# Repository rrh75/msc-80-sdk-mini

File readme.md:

# MSC-80 mini 8080A single board computer
This is a modified version of old Intel MSC-80 SDK, which utilize the Intel 8080A 8-bit processor. In this modification I tried to reduce size of pcb and number of ICs to minimum.

I have a bunch of old soviet era 8080 CPU clones, which are relatively chip now.
In current revision 74LS93 divider was replaces by 74LS92 divider, with is naturally /12, /6 or /3 divider. The board on picture below shows previous version with /16 divider (КР1553ИЕ5), configurated as /6.

The board has 2KB of UV EEPROM, 2KB of SRAM and 8251 UART controller for communication with console. In this version I used a 16,588MHz crystal to get the 1,8432MHz clock output, which could be divided by 6 or by 12 ro get correct baudrates.
Adress decoding also simplified comparing to original design and done by 3NAND gates. The address map are follow:
* ROM: 0000H-07FFH
* RAM: 1000H-17FFH
* UART: 0FAH
  
This version of board does not provide address buffering, but it is enough to work with onboard chips.
Communication with terminal program on the host computer is done via com port. Depending of the software and divide ratio it could be up to 19200 kb/s, RTS/CTS handshake, 8n1.

Since the processor use three voltages to operate, the board has build-in -5V charge pump circuit, but still required +5V and +12V. I used simple step-up converter to get +12V from +5V, but it was mounted outside the board. Power consumption from +5V is about 600 mA.
# Software
I've tried this board with original firmware, but since it was very old and intended to work with teletype, original monitor have very limited set of commands.

I found nice solution with GW monitor, with small modifications of addresses in source code it is also work and feet in existing ROM.

There also simple test program to test the 8251 communication functions.
Also I want to try 1K BASIC on this board.

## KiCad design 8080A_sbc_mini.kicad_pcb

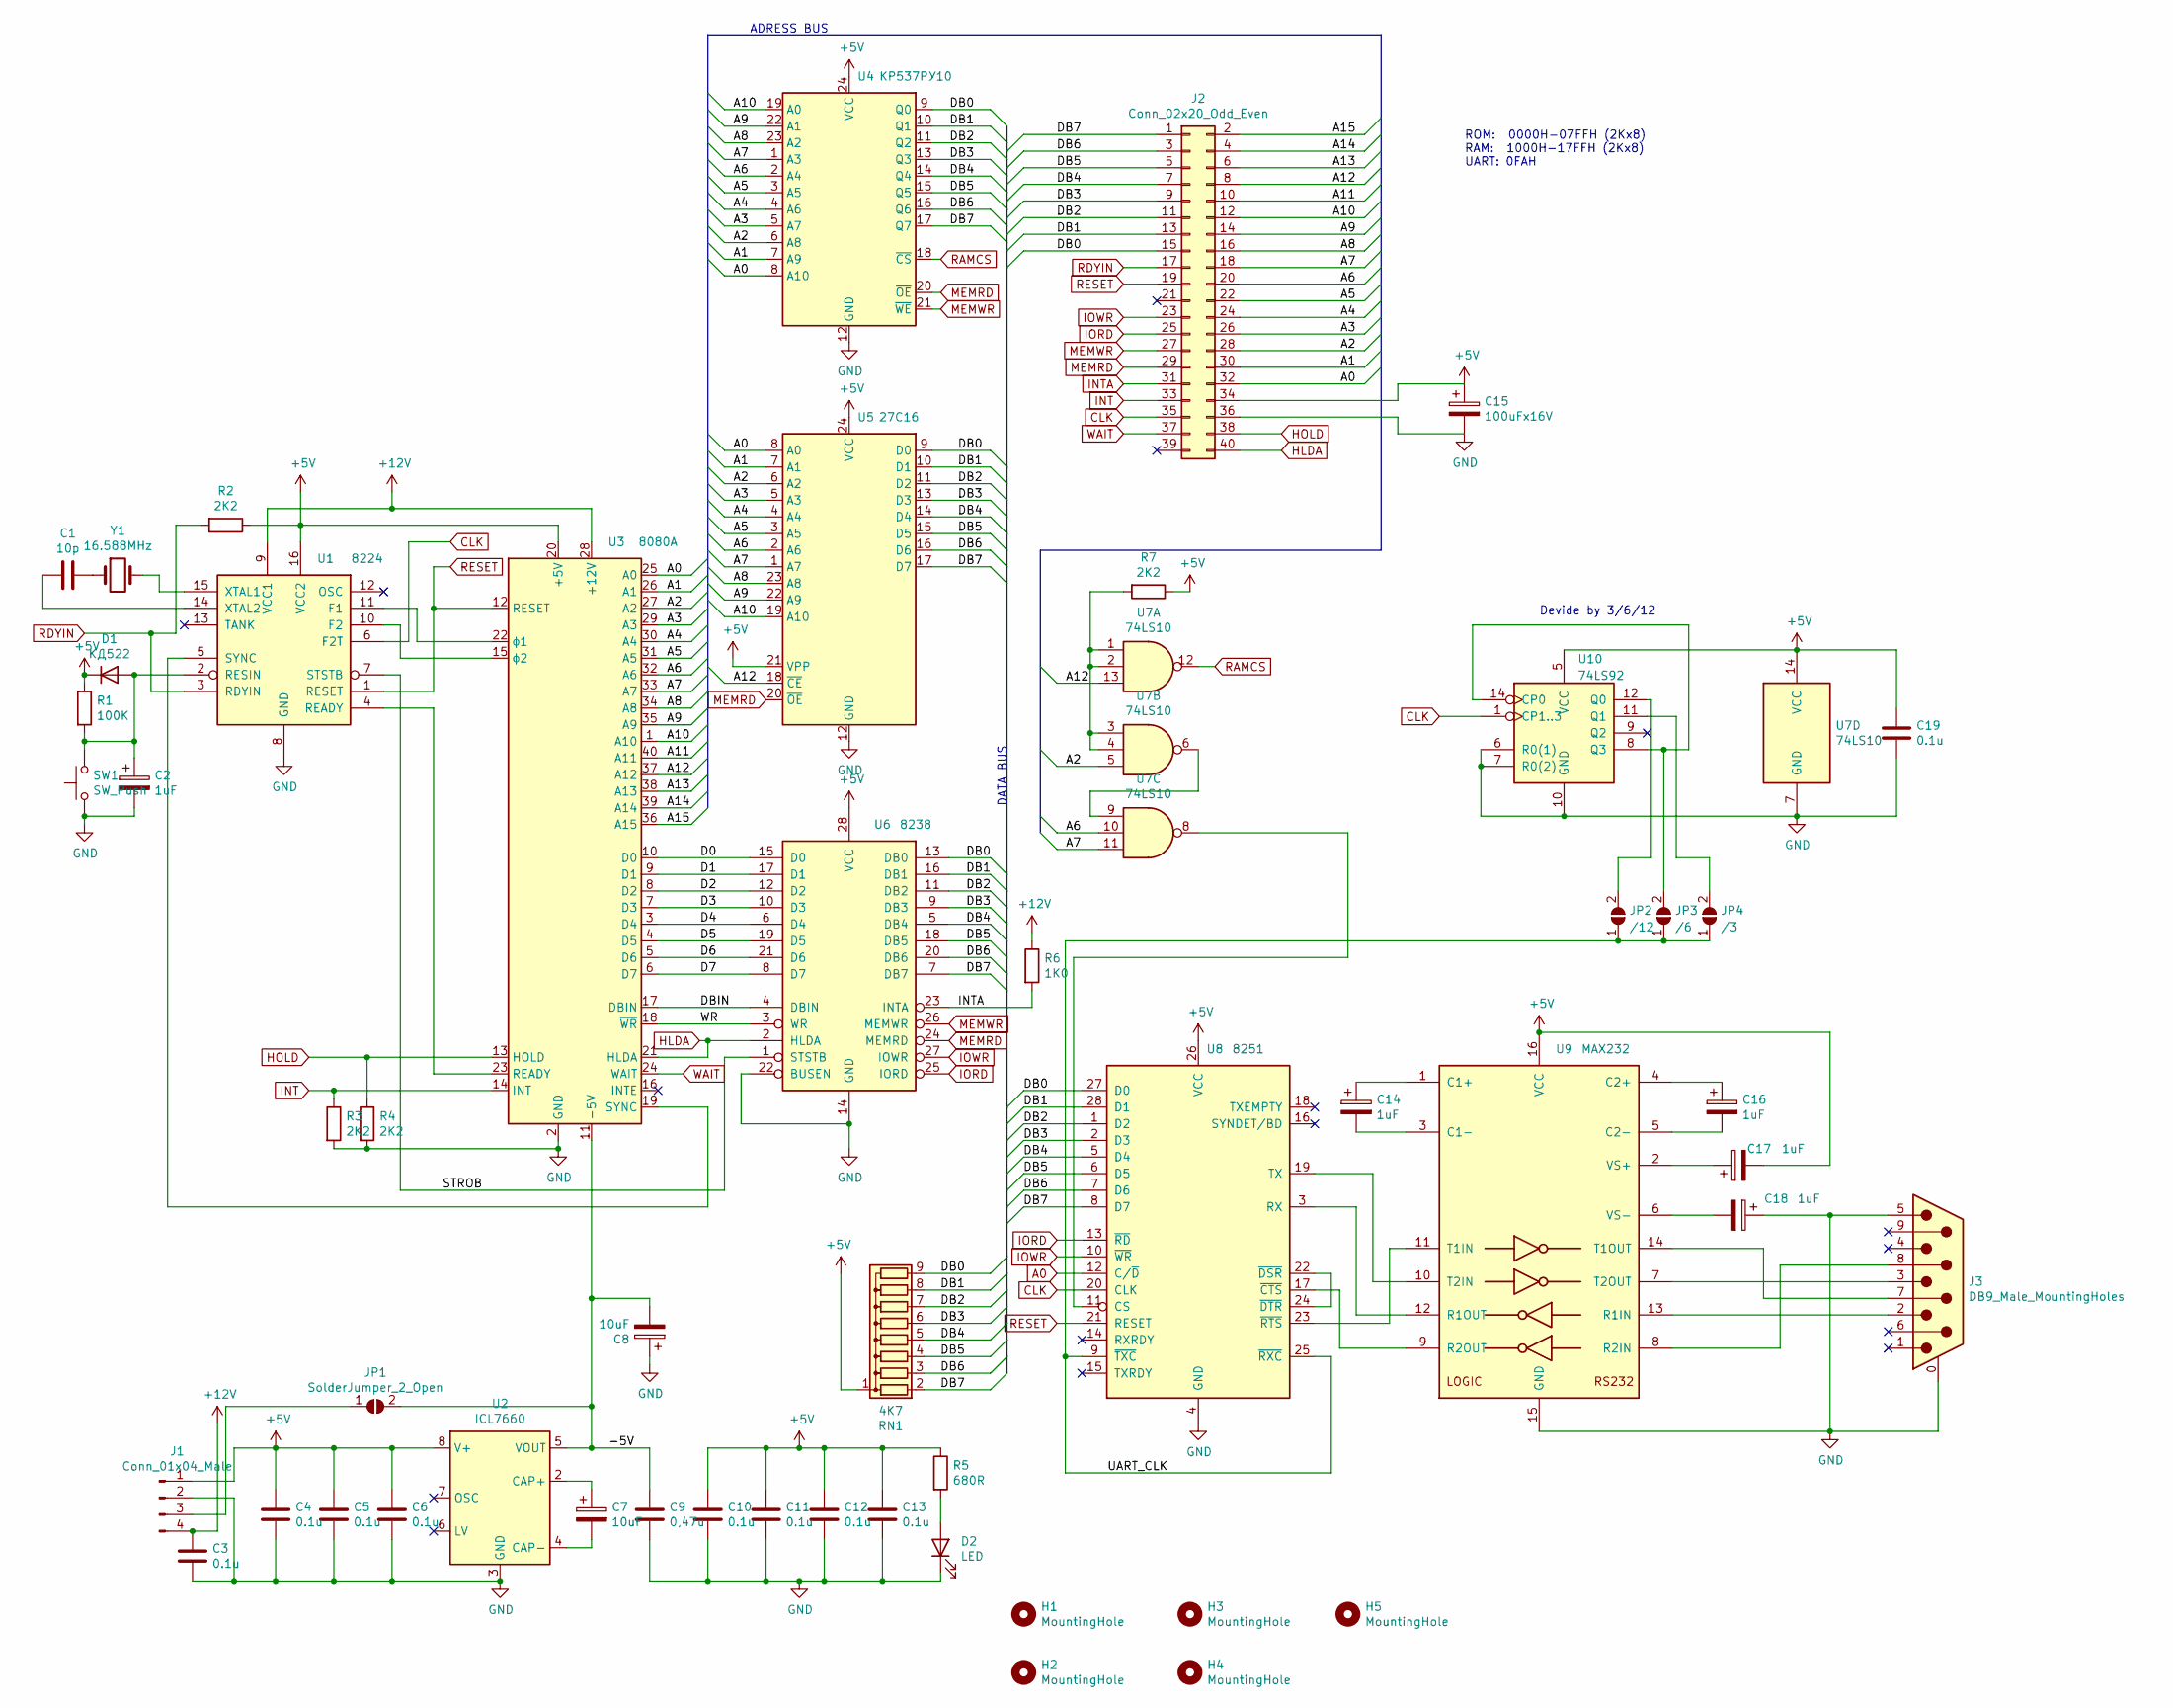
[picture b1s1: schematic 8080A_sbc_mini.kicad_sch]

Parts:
C1: 10p; C_Disc_D4.3mm_W1.9mm_P5.00mm
C2, C14, C16, C17, C18: 1uF; CP_Radial_D4.0mm_P2.00mm
C3, C4, C5, C6, C10, C11, C12, C13, C19: 0.1u; C_Disc_D4.3mm_W1.9mm_P5.00mm
C7, C8: 10uF; CP_Radial_D4.0mm_P2.00mm
C9: 0,47u; C_Disc_D4.3mm_W1.9mm_P5.00mm
C15: 100uFx16V; CP_Radial_D5.0mm_P2.00mm
D1: КД522; D_DO-35_SOD27_P7.62mm_Horizontal
D2: LED; LED_D3.0mm
H1, H2, H3, H4, H5: MountingHole; MountingHole_2.7mm_M2.5
J1: Conn_01x04_Male; Pin_Header_Angled_1x04_Pitch2.54mm
J2: Conn_02x20_Odd_Even; Pin_Header_Straight_2x20_Pitch2.54mm
J3: DB9_Male_MountingHoles; DSUB-9_Male_Horizontal_P2.77x2.84mm_EdgePinOffset7.70mm_Hou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
JP1: SolderJumper_2_Open; SolderJumper-2_P1.3mm_Open_RoundedPad1.0x1.5mm
JP2: /12; SolderJumper-2_P1.3mm_Open_RoundedPad1.0x1.5mm
JP3: /6; SolderJumper-2_P1.3mm_Open_RoundedPad1.0x1.5mm
JP4: /3; SolderJumper-2_P1.3mm_Open_RoundedPad1.0x1.5mm
R1: 100K; R_Axial_DIN0207_L6.3mm_D2.5mm_P7.62mm_Horizontal
R2, R3, R4, R7: 2K2; R_Axial_DIN0207_L6.3mm_D2.5mm_P7.62mm_Horizontal
R5: 680R; R_Axial_DIN0207_L6.3mm_D2.5mm_P7.62mm_Horizontal
R6: 1K0; R_Axial_DIN0207_L6.3mm_D2.5mm_P7.62mm_Horizontal
RN1: 4K7; R_Array_SIP9
SW1: SW_Push; SW_Tactile_SKHH_Angled
U1: 8224; DIP-16_W7.62mm
U2: ICL7660; DIP-8_W7.62mm
U3: 8080A; DIP-40_W15.24mm
U4: КР537РУ10; DIP-24_W15.24mm
U5: 27C16; DIP-24_W15.24mm
U6: 8238; DIP-28_W15.24mm
U7: 74LS10
U8: 8251; DIP-28_W15.24mm
U9: MAX232; DIP-16_W7.62mm
U10: 74LS92; DIP-14_W7.62mm
Y1: 16.588MHz; Crystal_HC49-U_Vertical

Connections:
+5V: C4.1, C5.1, C6.1, C10.1, C11.1, C12.1, C13.1, C15.1, C17.2, C19.1, D1.1 (K), J1.1, J2.34, R1.1, R2.1, R5.1, R7.1, RN1.1 (common), U1.16 (VCC2), U2.8 (V+), U3.20 (+5V), U4.24 (VCC), U5.21 (VPP), U5.24 (VCC), U6.28 (VCC), U7.14 (VCC), U8.26 (VCC), U9.16 (VCC), U10.5 (VCC)
+12V: C3.1, J1.4, R6.1, U1.9 (VCC1), U3.28 (+12V)
/-5V: C8.2, C9.1, JP1.2 (B), U2.5 (VOUT), U3.11 (-5V)
/A1: J2.30, U3.26 (A1), U4.7 (A9), U5.7 (A1)
/A2: J2.28, U3.27 (A2), U4.6 (A8), U5.6 (A2), U7.5
/A3: J2.26, U3.29 (A3), U4.5 (A7), U5.5 (A3)
/A4: J2.24, U3.30 (A4), U4.4 (A6), U5.4 (A4)
/A5: J2.22, U3.31 (A5), U4.3 (A5), U5.3 (A5)
/A6: J2.20, U3.32 (A6), U4.2 (A4), U5.2 (A6), U7.10
/A7: J2.18, U3.33 (A7), U4.1 (A3), U5.1 (A7), U7.11
/A8: J2.16, U3.34 (A8), U4.23 (A2), U5.23 (A8)
/A9: J2.14, U3.35 (A9), U4.22 (A1), U5.22 (A9)
/A10: J2.12, U3.1 (A10), U4.19 (A0), U5.19 (A10)
/A11: J2.10, U3.40 (A11)
/A12: J2.8, U3.37 (A12), U5.18 (~CE), U7.13
/A13: J2.6, U3.38 (A13)
/A14: J2.4, U3.39 (A14)
/A15: J2.2, U3.36 (A15)
/D0: U3.10 (D0), U6.15 (D0)
/D1: U3.9 (D1), U6.17 (D1)
/D2: U3.8 (D2), U6.12 (D2)
/D3: U3.7 (D3), U6.10 (D3)
/D4: U3.3 (D4), U6.6 (D4)
/D5: U3.4 (D5), U6.19 (D5)
/D6: U3.5 (D6), U6.21 (D6)
/D7: U3.6 (D7), U6.8 (D7)
/DB0: J2.15, RN1.9 (R8), U4.9 (Q0), U5.9 (D0), U6.13 (DB0), U8.27 (D0)
/DB1: J2.13, RN1.8 (R7), U4.10 (Q1), U5.10 (D1), U6.16 (DB1), U8.28 (D1)
/DB2: J2.11, RN1.7 (R6), U4.11 (Q2), U5.11 (D2), U6.11 (DB2), U8.1 (D2)
/DB3: J2.9, RN1.6 (R5), U4.13 (Q3), U5.13 (D3), U6.9 (DB3), U8.2 (D3)
/DB4: J2.7, RN1.5 (R4), U4.14 (Q4), U5.14 (D4), U6.5 (DB4), U8.5 (D4)
/DB5: J2.5, RN1.4 (R3), U4.15 (Q5), U5.15 (D5), U6.18 (DB5), U8.6 (D5)
/DB6: J2.3, RN1.3 (R2), U4.16 (Q6), U5.16 (D6), U6.20 (DB6), U8.7 (D6)
/DB7: J2.1, RN1.2 (R1), U4.17 (Q7), U5.17 (D7), U6.7 (DB7), U8.8 (D7)
/DBIN: U3.17 (DBIN), U6.4 (DBIN)
/STROB: U1.7 (STSTB), U6.1 (STSTB)
/UART_CLK: JP2.1 (A), JP3.1 (A), JP4.1 (A), U8.9 (~TXC), U8.25 (~RXC)
/WR: U3.18 (~WR), U6.3 (WR)
A0: J2.32, U3.25 (A0), U4.8 (A10), U5.8 (A0), U8.12 (C/~D)
CLK: J2.35, U1.6 (F2T), U8.20 (CLK), U10.1 (CP1..3)
GND: C2.2, C3.2, C4.2, C5.2, C6.2, C8.1, C9.2, C10.2, C11.2, C12.2, C13.2, C15.2, C18.1, C19.2, D2.1 (K), J1.2, J2.36, J3.0 (PAD), J3.5, R3.2, R4.2, SW1.1, U1.8 (GND), U2.3 (GND), U3.2 (GND), U4.12 (GND), U5.12 (GND), U6.14 (GND), U6.22 (BUSEN), U7.7 (GND), U8.4 (GND), U9.15 (GND), U10.6 (R0(1)), U10.7 (R0(2)), U10.10 (GND)
HLDA: J2.40, U3.21 (HLDA), U6.2 (HLDA)
HOLD: J2.38, R4.1, U3.13 (HOLD)
INT: J2.33, R3.1, U3.14 (INT)
INTA: J2.31, R6.2, U6.23 (INTA)
IORD: J2.25, U6.25 (IORD), U8.13 (~RD)
IOWR: J2.23, U6.27 (IOWR), U8.10 (~WR)
MEMRD: J2.29, U4.20 (~OE), U5.20 (~OE), U6.24 (MEMRD)
MEMWR: J2.27, U4.21 (~WE), U6.26 (MEMWR)
unnamed: C1.1, Y1.1
unnamed: C1.2, U1.14 (XTAL2)
unnamed: C2.1, D1.2 (A), R1.2, SW1.2, U1.2 (RESIN)
unnamed: C7.1, U2.2 (CAP+)
unnamed: C7.2, U2.4 (CAP-)
unnamed: C14.1, U9.1 (C1+)
unnamed: C14.2, U9.3 (C1-)
unnamed: C16.1, U9.4 (C2+)
unnamed: C16.2, U9.5 (C2-)
unnamed: C17.1, U9.2 (VS+)
unnamed: C18.2, U9.6 (VS-)
unnamed: D2.2 (A), R5.2
unnamed: J1.3, JP1.1 (A)
unnamed: J3.2, U9.13 (R1IN)
unnamed: J3.3, U9.7 (T2OUT)
unnamed: J3.7, U9.14 (T1OUT)
unnamed: J3.8, U9.8 (R2IN)
unnamed: JP2.2 (B), U10.12 (Q0)
unnamed: JP3.2 (B), U10.8 (Q3), U10.14 (CP0)
unnamed: JP4.2 (B), U10.11 (Q1)
unnamed: R7.2, U7.1, U7.2, U7.3, U7.4
unnamed: U1.4 (READY), U3.23 (READY)
unnamed: U1.5 (SYNC), U3.19 (SYNC)
unnamed: U1.10 (F2), U3.15 (ϕ2)
unnamed: U1.11 (F1), U3.22 (ϕ1)
unnamed: U1.15 (XTAL1), Y1.2
unnamed: U7.6, U7.9
unnamed: U7.8, U8.11 (CS)
unnamed: U8.3 (RX), U9.12 (R1OUT)
unnamed: U8.17 (~CTS), U9.9 (R2OUT)
unnamed: U8.19 (TX), U9.10 (T2IN)
unnamed: U8.22 (~DSR), U8.24 (~DTR)
unnamed: U8.23 (~RTS), U9.11 (T1IN)
RAMCS: U4.18 (~CS), U7.12
RDYIN: J2.17, R2.2, U1.3 (RDYIN)
RESET: J2.19, U1.1 (RESET), U3.12 (RESET), U8.21 (RESET)
WAIT: J2.37, U3.24 (WAIT)

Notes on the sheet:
ROM: 0000H-07FFH (2Kx8) RAM: 1000H-17FFH (2Kx8) UART: 0FAH
Devide by 3/6/12
DATA BUS
ADRESS BUS

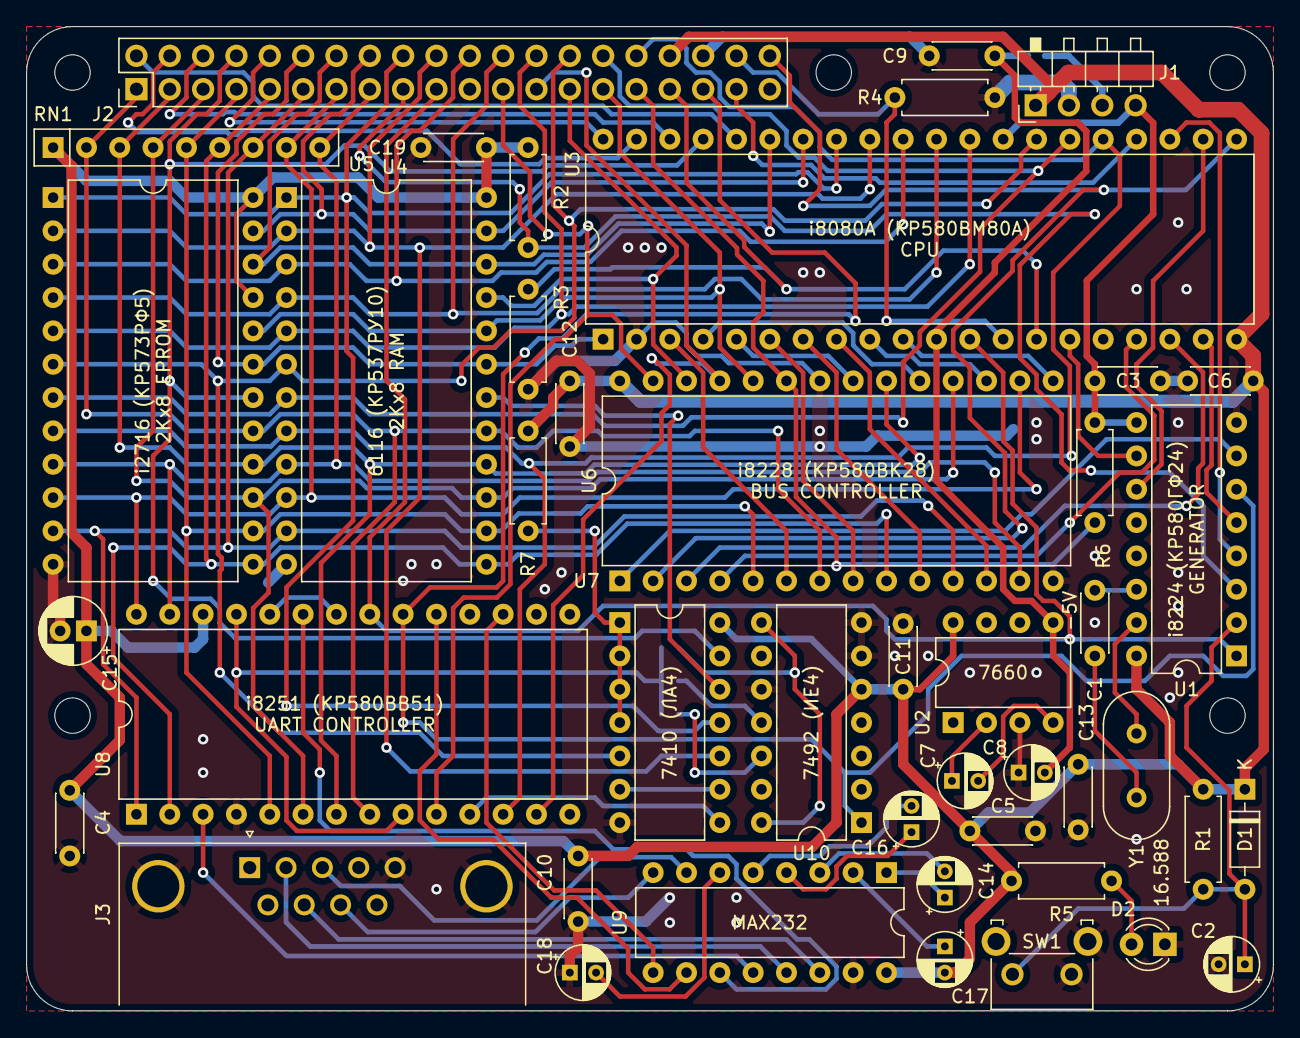
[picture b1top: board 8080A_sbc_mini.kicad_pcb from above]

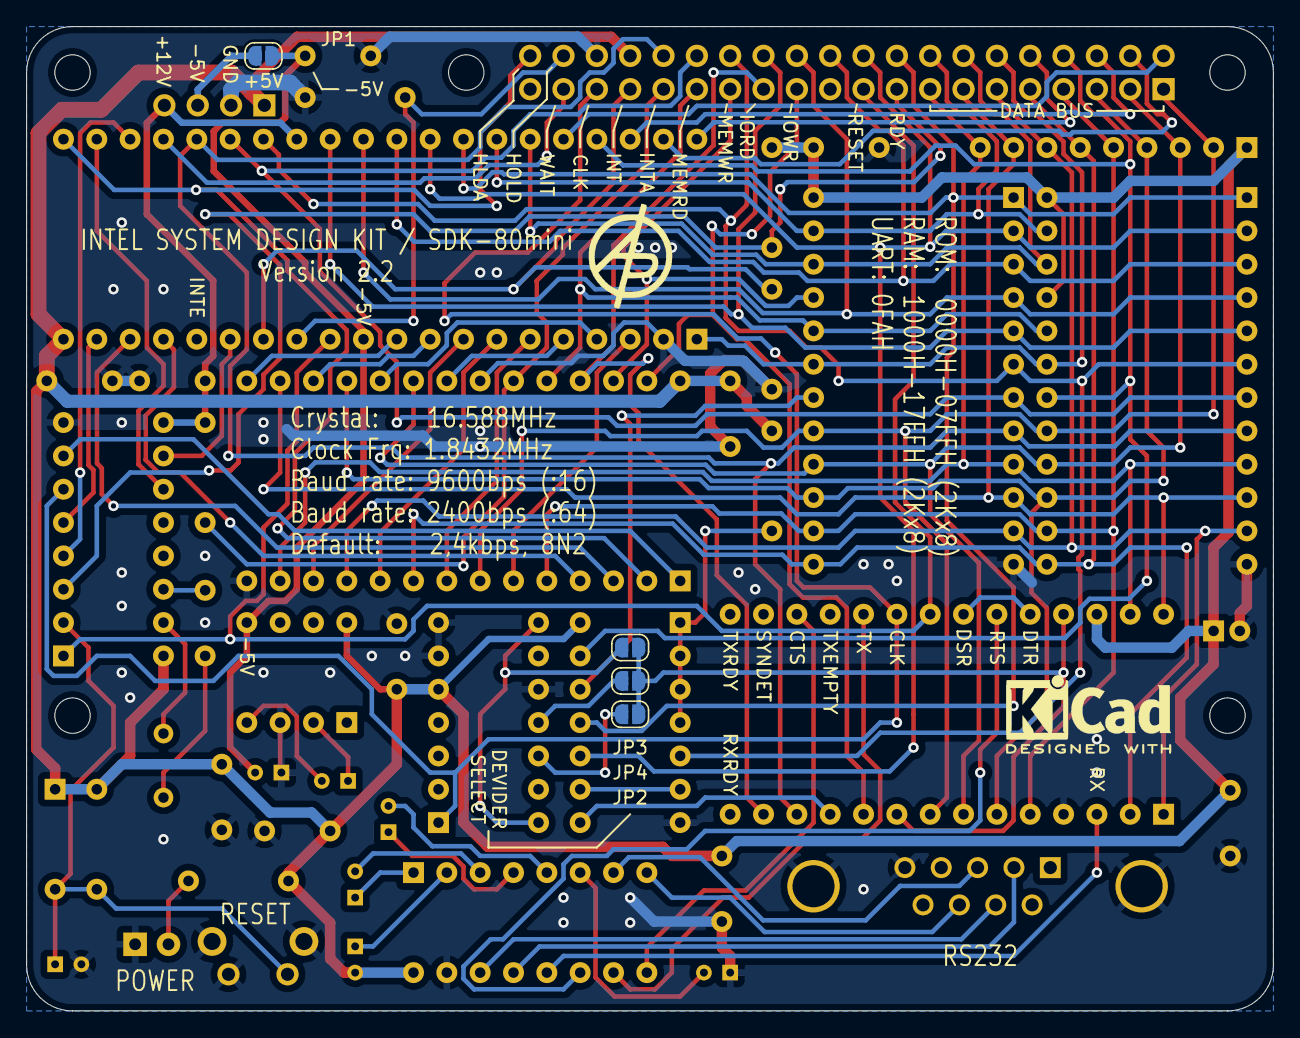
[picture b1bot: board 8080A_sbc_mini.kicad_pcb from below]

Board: 2 copper layers, 95.0 x 75.0 mm, 53 parts (4 on the bottom side), 86 nets.
